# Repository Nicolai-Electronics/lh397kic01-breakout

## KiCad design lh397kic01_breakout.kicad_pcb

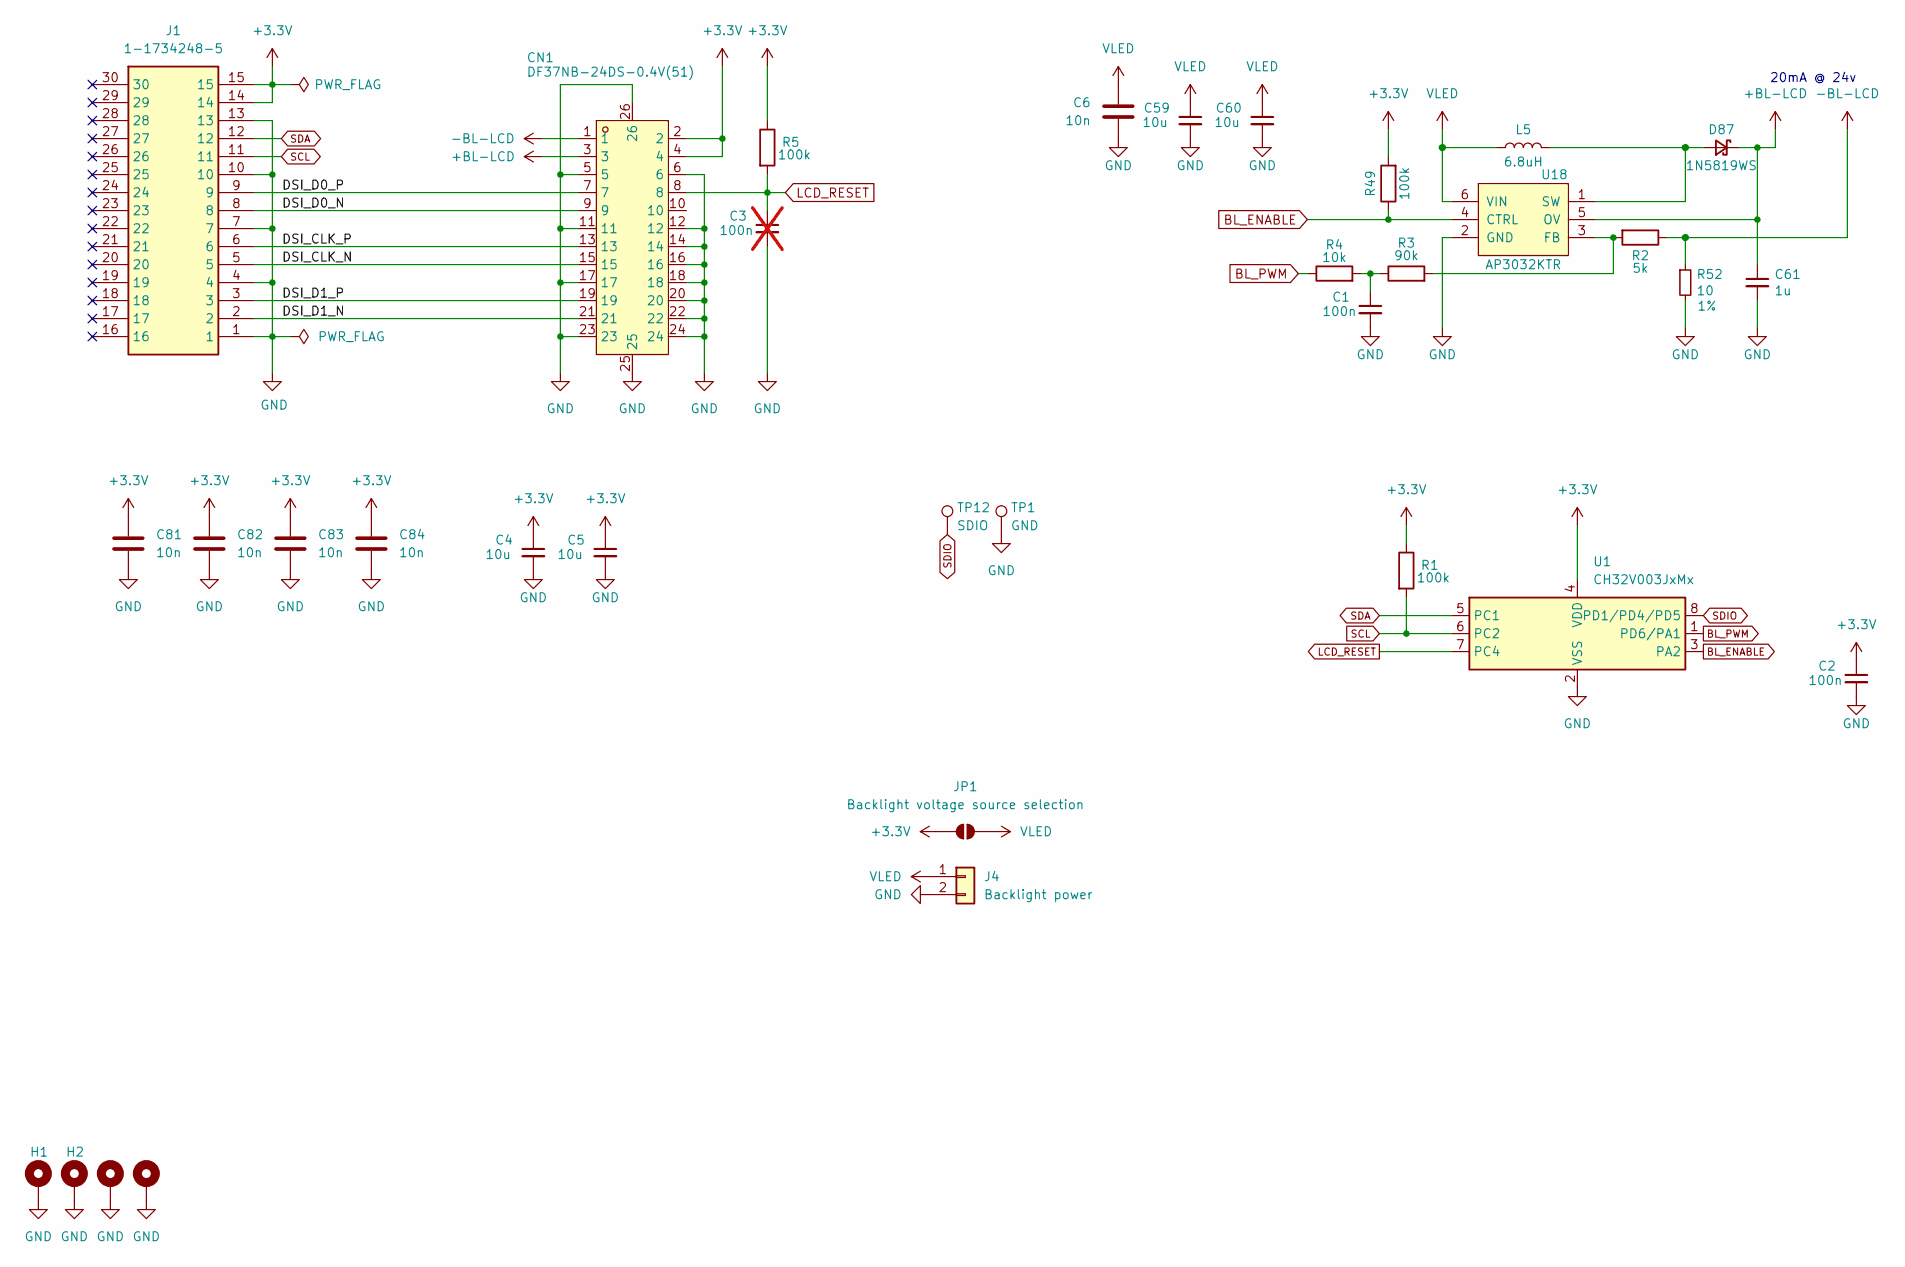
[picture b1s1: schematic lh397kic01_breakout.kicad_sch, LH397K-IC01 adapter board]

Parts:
C1, C2: 100n; C_0402_1005Metric; LCSC C307331
C3: 100n; C_0402_1005Metric; LCSC C307331; not fitted
C4, C5, C59, C60: 10u; C_0805_2012Metric; LCSC C3039694
C6, C81, C82, C83, C84: 10n; C_0402_1005Metric; LCSC C15195
C61: 1u; C_0603_1608Metric; LCSC C5199872
CN1: DF37NB-24DS-0.4V(51); CONN-SMD_DF37NB-24DS-0.4V; LCSC C3036280
D87: 1N5819WS; D_SOD-323; LCSC C369937
H1, H2, H3, H4: MountingHole_2.2mm_M2_DIN965_Pad
J1: 1-1734248-5; 117342485; Mouser Part Number 571-1-1734248-5
J4: Backlight power; PinHeader_1x02_P2.54mm_Vertical
JP1: Backlight voltage source selection; SolderJumper-2_P1.3mm_Open_RoundedPad1.0x1.5mm
L5: 6.8uH; IND-SMD_L4.0-W4.0; LCSC C520306
R1, R5, R49: 100k; R_0402_1005Metric; LCSC C25741
R2: 5k; R_0402_1005Metric
R3: 90k; R_0402_1005Metric
R4: 10k; R_0402_1005Metric
R52: 10; R_0402_1005Metric; LCSC C25077
TP1: GND; TestPoint_Pad_D1.0mm
TP12: SDIO; TestPoint_Pad_D1.0mm
U1: CH32V003JxMx; JEITA_SOIC-8_3.9x4.9mm_P1.27mm
U18: AP3032KTR; SOT-23-6; LCSC C264086

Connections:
+3.3V: C2.1, C4.1, C5.1, C81.1, C82.1, C83.1, C84.1, CN1.2, CN1.4, J1.14, J1.15, JP1.2 (B), R1.1, R5.1, R49.2, U1.4 (VDD)
+BL-LCD: C61.1, CN1.3, D87.1 (K), U18.5 (OV)
-BL-LCD: CN1.1, R2.1, R52.1
/DSI_CLK_N: CN1.15, J1.5
/DSI_CLK_P: CN1.13, J1.6
/DSI_D0_N: CN1.9, J1.8
/DSI_D0_P: CN1.7, J1.9
/DSI_D1_N: CN1.21, J1.2
/DSI_D1_P: CN1.19, J1.3
BL_ENABLE: R49.1, U1.3 (PA2), U18.4 (CTRL)
BL_PWM: R4.1, U1.1 (PD6/PA1)
GND: C1.2, C2.2, C3.2, C4.2, C5.2, C6.2, C59.2, C60.2, C61.2, C81.2, C82.2, C83.2, C84.2, CN1.5, CN1.6, CN1.11, CN1.12, CN1.14, CN1.16, CN1.17, CN1.18, CN1.20, CN1.22, CN1.23, CN1.24, CN1.25, CN1.26, H1.1, H2.1, H3.1, H4.1, J1.1, J1.4, J1.7, J1.10, J1.13, J4.2, R52.2, TP1.1, U1.2 (VSS), U18.2 (GND)
LCD_RESET: C3.1, CN1.8, R5.2, U1.7 (PC4)
unnamed: C1.1, R3.1, R4.2
unnamed: D87.2 (A), L5.2, U18.1 (SW)
unnamed: R2.2, R3.2, U18.3 (FB)
SCL: J1.11, R1.2, U1.6 (PC2)
SDA: J1.12, U1.5 (PC1)
SDIO: TP12.1, U1.8 (PD1/PD4/PD5)
VLED: C6.1, C59.1, C60.1, J4.1, JP1.1 (A), L5.1, U18.6 (VIN)

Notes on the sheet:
20mA @ 24v

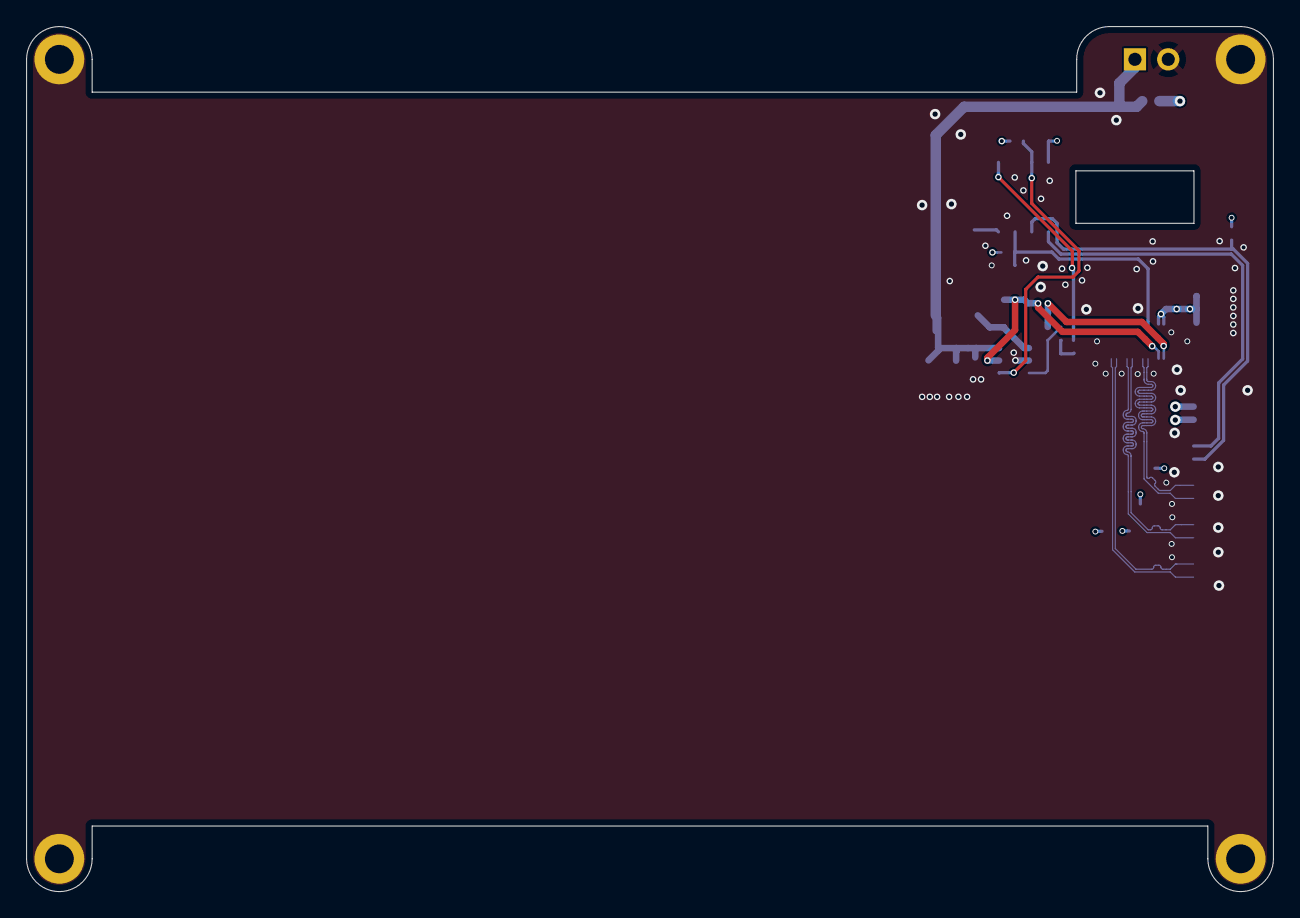
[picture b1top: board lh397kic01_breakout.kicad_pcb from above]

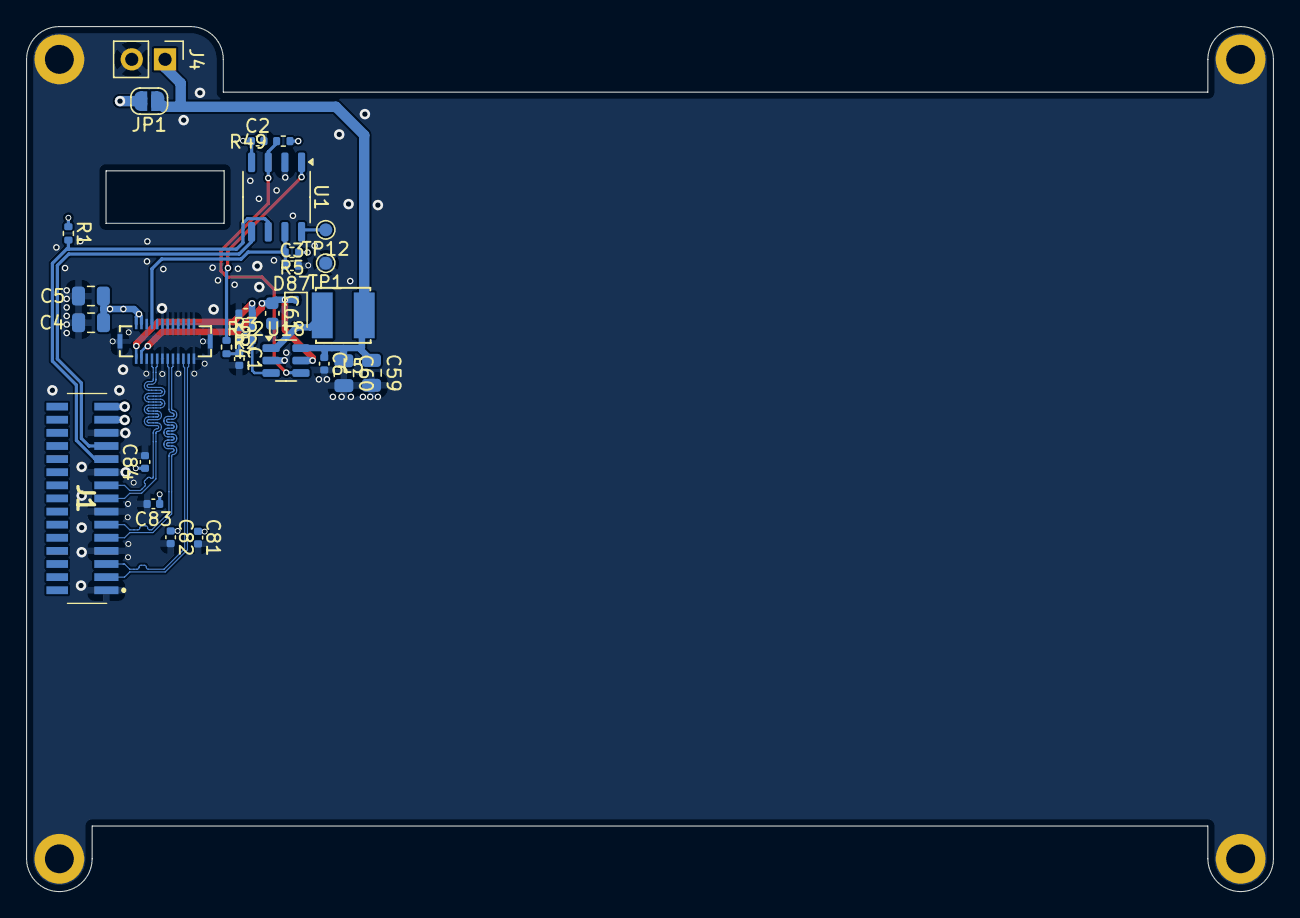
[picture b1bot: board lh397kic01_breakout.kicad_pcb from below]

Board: 4 copper layers, 95.1 x 66.0 mm, 34 parts (30 on the bottom side), 20 nets.

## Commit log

2025-10-28 Changes based on feedback
